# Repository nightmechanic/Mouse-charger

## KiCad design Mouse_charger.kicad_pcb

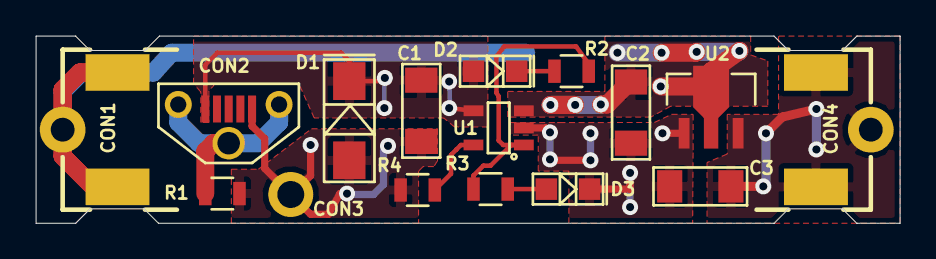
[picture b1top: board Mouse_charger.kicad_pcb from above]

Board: 2 copper layers, 48.0 x 10.4 mm, 17 parts (1 on the bottom side), 9 nets.

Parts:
C1, C2, C3: 10uF 35V; mm_3216
CON1, CON4: AAA_Bat_PC_con; Keystone_597_narrow
CON2: Molex_105133-0011; Molex_105122_0011_no_slots
CON3: 1.5mm_PTH
D1: P4SMA6.8A (TVS UNI); DO-214AC
D2: Amber LED; SMD_MiniLED
D3: Green LED; SMD_MiniLED
R1: ZEROHM; R_0805
R2, R3: 1.3k; R_0805
R4: 4.99k; R_0805
U1: MCP73831-2ACI/OT; MCP_SOT-23-5
U2: MCP1700-3002E/MB; MCP_SOT-89
VAL: REF; Gears_F.SilkS_10mm_flipped

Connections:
/V_3V0: C3.1, CON4.1, CON4.2, CON4.3, U2.3
/V_batt: C2.1, CON1.1, CON1.2, CON1.3, U1.3, U2.2
/V_bus: C1.1, CON2.1, D1.2, D2.1, U1.4
GND: C1.2, C2.2, C3.2, CON2.5, CON3.1, D1.1, D3.2, R1.1, R4.2, U1.2, U2.1
unnamed: CON2.S_1, CON2.S_2, CON2.S_3, R1.2
unnamed: D2.2, R2.1
unnamed: D3.1, R3.2
unnamed: R2.2, R3.1, U1.1
unnamed: R4.1, U1.5

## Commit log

2015-01-12 version 1
2015-01-12 added private 3d models
2015-01-12 added 3d model location for Mac
2015-01-12 error...
2015-01-12 Added screw as positive bat terminal
2015-01-13 Narrow outline
2015-01-14 Mac OS 3d
2015-01-14 changed fill zone clearance
2015-01-14 Added V_bus plane on bottom
    Added V_bus plane on bottom for better U1 heat dissipation
2015-01-22 wrl generation
2015-02-02 ready to fab
2015-04-05 schematic pdf
2015-04-06 PCB page settings

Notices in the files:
Mouse_charger.kicad_pcb:
© Magic Mouse Charger
